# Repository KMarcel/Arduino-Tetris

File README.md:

# Arduino Matrix Tetris

Dear Ladies and Gentlemen
I wanted to create a little Game Console. The first Game for this Game Console is Tetris

The Output is realized by LED 8x16 Matrix.
The Controller there i use is the Arduino Nano

Here is the Schematic

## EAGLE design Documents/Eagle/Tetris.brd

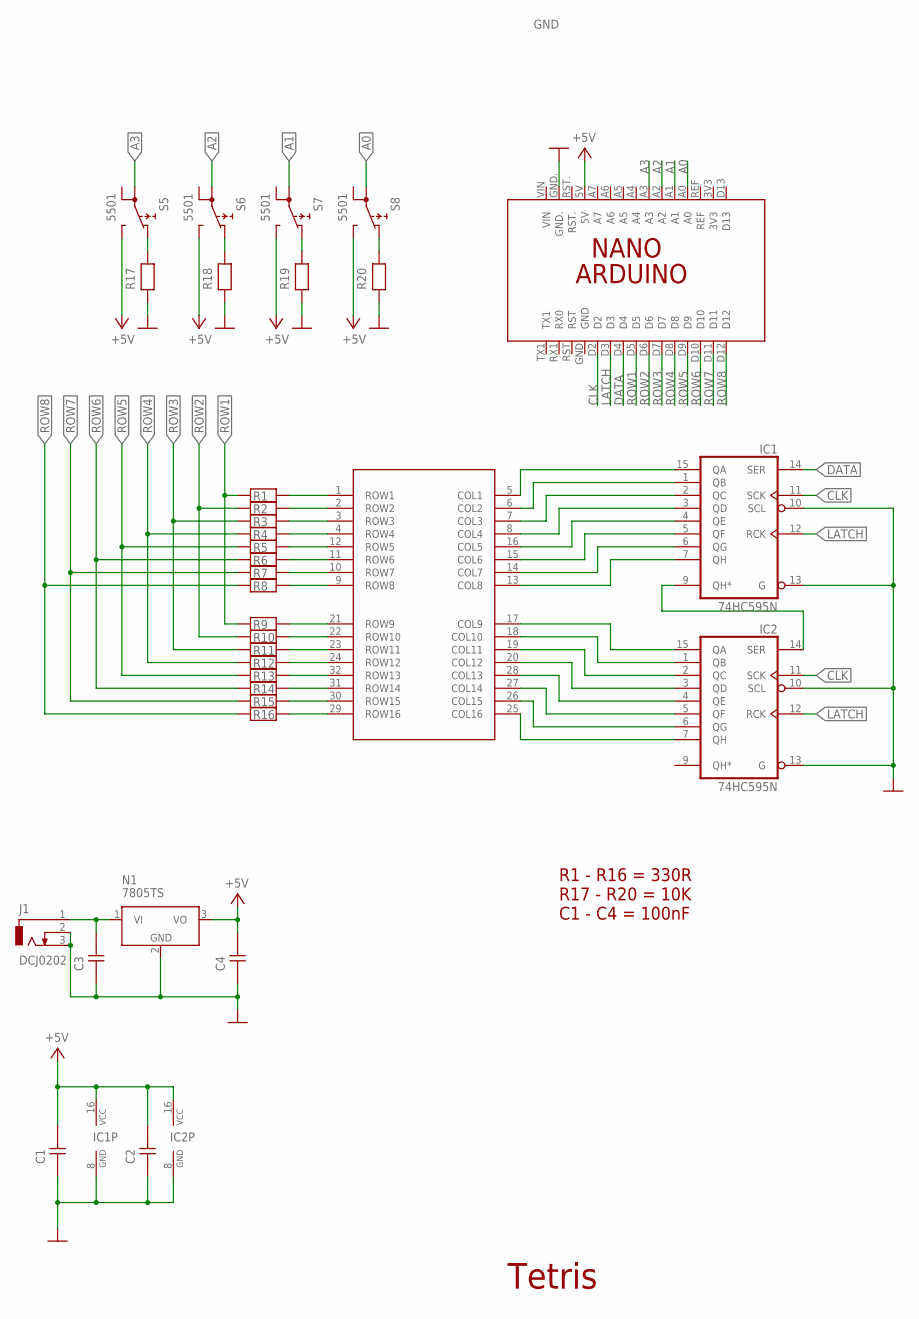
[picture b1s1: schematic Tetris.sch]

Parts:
C1, C2, C3, C4: C-7.5; C-7,5
IC1, IC2: 74HC595N; DIL16
J1: DCJ0202
N1: 7805TS; TO-220S
PCB1: ARDUINO_NANO
R1, R2, R3, R4, R5, R6, R7, R8, R9, R10, R11, R12, R13, R14, R15, R16, R17, R18, R19, R20: R-10
S5, S6, S7, S8: 5501
U$9: DOT_MATRIX; SH

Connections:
+5V: C1.2, C2.2, C4.2, IC1.16 (VCC), IC2.16 (VCC), N1.3 (VO), PCB1.5V, S5.NC (NO), S6.NC (NO), S7.NC (NO), S8.NC (NO)
A0: PCB1.A0, S8.1A
A1: PCB1.A1, S7.1A
A2: PCB1.A2, S6.1A
A3: PCB1.A3, S5.1A
CLK: IC1.11 (SCK), IC2.11 (SCK), PCB1.D2
DATA: IC1.14 (SER), PCB1.D4
GND: C1.1, C2.1, C3.1, C4.1, IC1.8 (GND), IC1.10 (SCL), IC1.13 (G), IC2.8 (GND), IC2.10 (SCL), IC2.13 (G), J1.2, J1.3, N1.2 (GND), PCB1.GND., R17.1, R18.1, R19.1, R20.1
LATCH: IC1.12 (RCK), IC2.12 (RCK), PCB1.D3
unnamed: IC2.15 (QA), U$9.17 (COL9)
unnamed: IC2.1 (QB), U$9.18 (COL10)
unnamed: IC2.2 (QC), U$9.19 (COL11)
unnamed: IC1.9 (QH*), IC2.14 (SER)
unnamed: C3.2, J1.1, N1.1 (VI)
unnamed: IC2.3 (QD), U$9.20 (COL12)
unnamed: IC2.4 (QE), U$9.28 (COL13)
unnamed: IC2.5 (QF), U$9.27 (COL14)
unnamed: IC2.6 (QG), U$9.26 (COL15)
unnamed: IC2.7 (QH), U$9.25 (COL16)
unnamed: IC1.7 (QH), U$9.13 (COL8)
unnamed: IC1.6 (QG), U$9.14 (COL7)
unnamed: IC1.5 (QF), U$9.15 (COL6)
unnamed: IC1.4 (QE), U$9.16 (COL5)
unnamed: IC1.3 (QD), U$9.8 (COL4)
unnamed: IC1.2 (QC), U$9.7 (COL3)
unnamed: IC1.1 (QB), U$9.6 (COL2)
unnamed: IC1.15 (QA), U$9.5 (COL1)
unnamed: R8.2, U$9.9 (ROW8)
unnamed: R7.2, U$9.10 (ROW7)
unnamed: R6.2, U$9.11 (ROW6)
unnamed: R5.2, U$9.12 (ROW5)
unnamed: R1.2, U$9.1 (ROW1)
unnamed: R2.2, U$9.2 (ROW2)
unnamed: R3.2, U$9.3 (ROW3)
unnamed: R4.2, U$9.4 (ROW4)
unnamed: R9.2, U$9.21 (ROW9)
unnamed: R10.2, U$9.22 (ROW10)
unnamed: R11.2, U$9.23 (ROW11)
unnamed: R12.2, U$9.24 (ROW12)
unnamed: R13.2, U$9.32 (ROW13)
unnamed: R14.2, U$9.31 (ROW14)
unnamed: R15.2, U$9.30 (ROW15)
unnamed: R16.2, U$9.29 (ROW16)
unnamed: R17.2, S5.NO (NC)
unnamed: R18.2, S6.NO (NC)
unnamed: R19.2, S7.NO (NC)
unnamed: R20.2, S8.NO (NC)
ROW1: PCB1.D5, R1.1, R9.1
ROW2: PCB1.D6, R2.1, R10.1
ROW3: PCB1.D7, R3.1, R11.1
ROW4: PCB1.D8, R4.1, R12.1
ROW5: PCB1.D9, R5.1, R13.1
ROW6: PCB1.D10, R6.1, R14.1
ROW7: PCB1.D11, R7.1, R15.1
ROW8: PCB1.D12, R8.1, R16.1

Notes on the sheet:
Tetris
R1 - R16 = 330R R17 - R20 = 10K C1 - C4 = 100nF

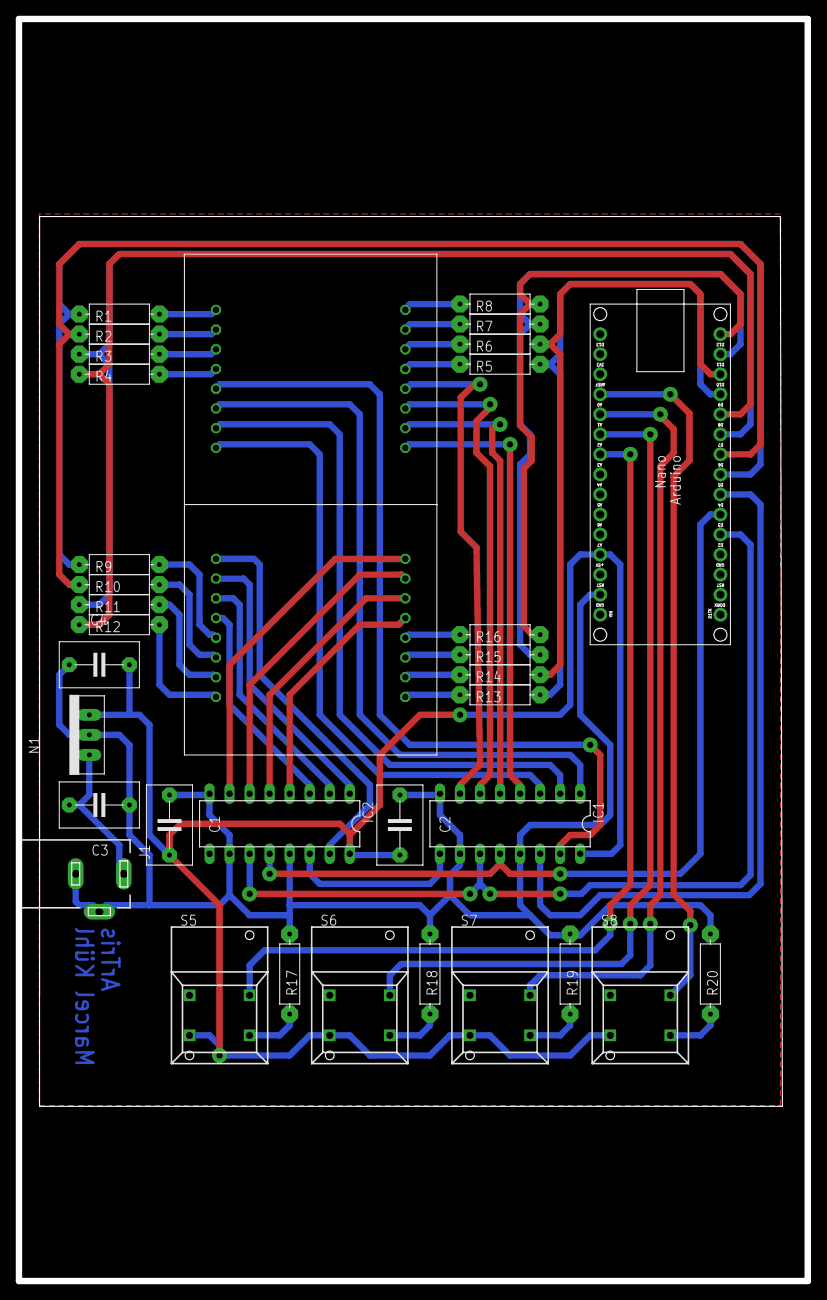
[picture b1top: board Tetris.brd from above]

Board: 2 copper layers, 100.0 x 160.0 mm, 34 parts (0 on the bottom side), 55 nets.

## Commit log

2017-05-02 Create k
